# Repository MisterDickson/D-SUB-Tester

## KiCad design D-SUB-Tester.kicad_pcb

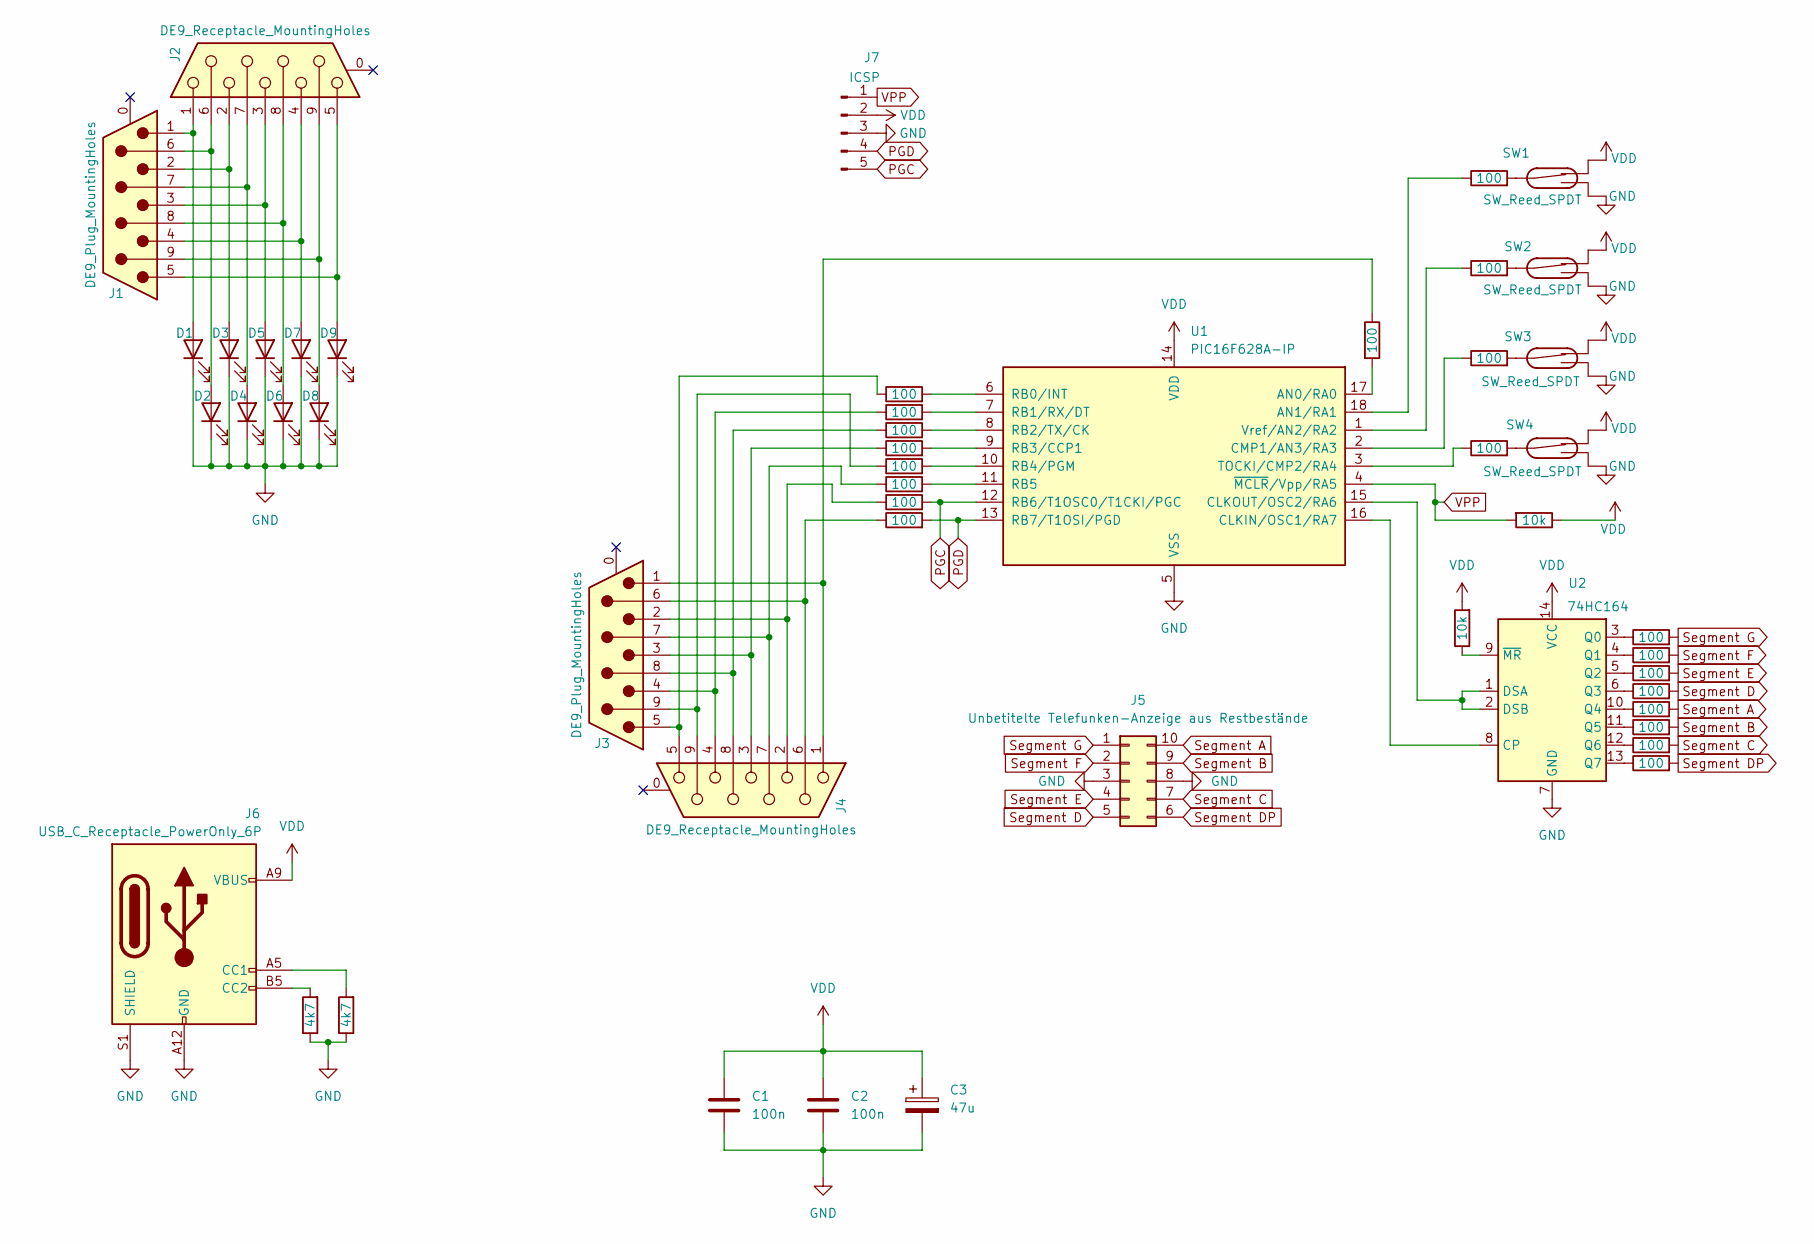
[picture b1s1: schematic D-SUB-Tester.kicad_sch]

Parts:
C1, C2: 100n; C_Disc_D7.0mm_W2.5mm_P5.00mm
C3: 47u; CP_Radial_D6.3mm_P2.50mm
D1, D2, D3, D4, D5, D6, D7, D8, D9: LED; LED_D3.0mm
J1, J3: DE9_Plug_MountingHoles; DSUB-9_Male_Horizontal_P2.77x2.84mm_EdgePinOffset7.70mm_Hou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
J2, J4: DE9_Receptacle_MountingHoles; DSUB-9_Female_Vertical_P2.77x2.84mm_MountingHoles
J5: Unbetitelte Telefunken-Anzeige aus Restbestände; DIP-10_W7.62mm_LongPads
J6: USB_C_Receptacle_PowerOnly_6P; USB_C_Receptacle_HRO_TYPE-C-31-M-17
J7: ICSP; PinHeader_1x05_P2.54mm_Vertical
R1, R2, R3, R4, R5, R6, R7, R8, R11, R12, R13, R14, R17, R18, R19, R20, R21, R22, R23, R24, R25: 100; R_Axial_DIN0411_L9.9mm_D3.6mm_P12.70mm_Horizontal
R9, R10: 4k7; R_Axial_DIN0411_L9.9mm_D3.6mm_P12.70mm_Horizontal
R15, R16: 10k; R_Axial_DIN0411_L9.9mm_D3.6mm_P12.70mm_Horizontal
SW1, SW2, SW3, SW4: SW_Reed_SPDT; SW_SPDT_CK_JS102011SAQN
U1: PIC16F628A-IP; DIP-18_W7.62mm_LongPads
U2: 74HC164; DIP-14_W7.62mm_LongPads

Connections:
GND: C1.2, C2.2, C3.2, D1.1 (K), D2.1 (K), D3.1 (K), D4.1 (K), D5.1 (K), D6.1 (K), D7.1 (K), D8.1 (K), D9.1 (K), J5.3, J5.8, J6.A12 (GND), J6.B12 (GND), J6.S1 (SHIELD), J7.3, R9.1, R10.1, SW1.3, SW2.3, SW3.3, SW4.3, U1.5 (VSS), U2.7 (GND)
unnamed: D1.2 (A), J1.1, J2.1
unnamed: D2.2 (A), J1.6, J2.6
unnamed: D3.2 (A), J1.2, J2.2
unnamed: D4.2 (A), J1.7, J2.7
unnamed: D5.2 (A), J1.3, J2.3
unnamed: D6.2 (A), J1.8, J2.8
unnamed: D7.2 (A), J1.4, J2.4
unnamed: D8.2 (A), J1.9, J2.9
unnamed: D9.2 (A), J1.5, J2.5
unnamed: J3.1, J4.1, R25.1
unnamed: J3.2, J4.2, R23.1
unnamed: J3.3, J4.3, R20.1
unnamed: J3.4, J4.4, R18.1
unnamed: J3.5, J4.5, R17.1
unnamed: J3.6, J4.6, R24.1
unnamed: J3.7, J4.7, R22.1
unnamed: J3.8, J4.8, R19.1
unnamed: J3.9, J4.9, R21.1
unnamed: J6.A5 (CC1), R10.2
unnamed: J6.B5 (CC2), R9.2
unnamed: R11.2, SW1.2
unnamed: R12.2, SW2.2
unnamed: R13.2, SW3.2
unnamed: R14.2, SW4.2
unnamed: R25.2, U1.17 (AN0/RA0)
unnamed: R11.1, U1.18 (AN1/RA1)
unnamed: U1.16 (CLKIN/OSC1/RA7), U2.8 (CP)
unnamed: U1.15 (CLKOUT/OSC2/RA6), U2.1 (DSA), U2.2 (DSB)
unnamed: R13.1, U1.2 (CMP1/AN3/RA3)
unnamed: R17.2, U1.6 (RB0/INT)
unnamed: R18.2, U1.7 (RB1/RX/DT)
unnamed: R19.2, U1.8 (RB2/TX/CK)
unnamed: R20.2, U1.9 (RB3/CCP1)
unnamed: R21.2, U1.10 (RB4/PGM)
unnamed: R22.2, U1.11 (RB5)
unnamed: R14.1, U1.3 (TOCKI/CMP2/RA4)
unnamed: R12.1, U1.1 (Vref/AN2/RA2)
unnamed: R1.1, U2.3 (Q0)
unnamed: R2.1, U2.4 (Q1)
unnamed: R3.1, U2.5 (Q2)
unnamed: R4.1, U2.6 (Q3)
unnamed: R5.1, U2.10 (Q4)
unnamed: R6.1, U2.11 (Q5)
unnamed: R7.1, U2.12 (Q6)
unnamed: R8.1, U2.13 (Q7)
unnamed: R15.1, U2.9 (~MR)
PGC: J7.5, R23.2, U1.12 (RB6/T1OSC0/T1CKI/PGC)
PGD: J7.4, R24.2, U1.13 (RB7/T1OSI/PGD)
Segment A: J5.10, R5.2
Segment B: J5.9, R6.2
Segment C: J5.7, R7.2
Segment D: J5.5, R4.2
Segment DP: J5.6, R8.2
Segment E: J5.4, R3.2
Segment F: J5.2, R2.2
Segment G: J5.1, R1.2
VDD: C1.1, C2.1, C3.1, J6.A9 (VBUS), J6.B9 (VBUS), J7.2, R15.2, R16.1, SW1.1, SW2.1, SW3.1, SW4.1, U1.14 (VDD), U2.14 (VCC)
VPP: J7.1, R16.2, U1.4 (~MCLR/Vpp/RA5)

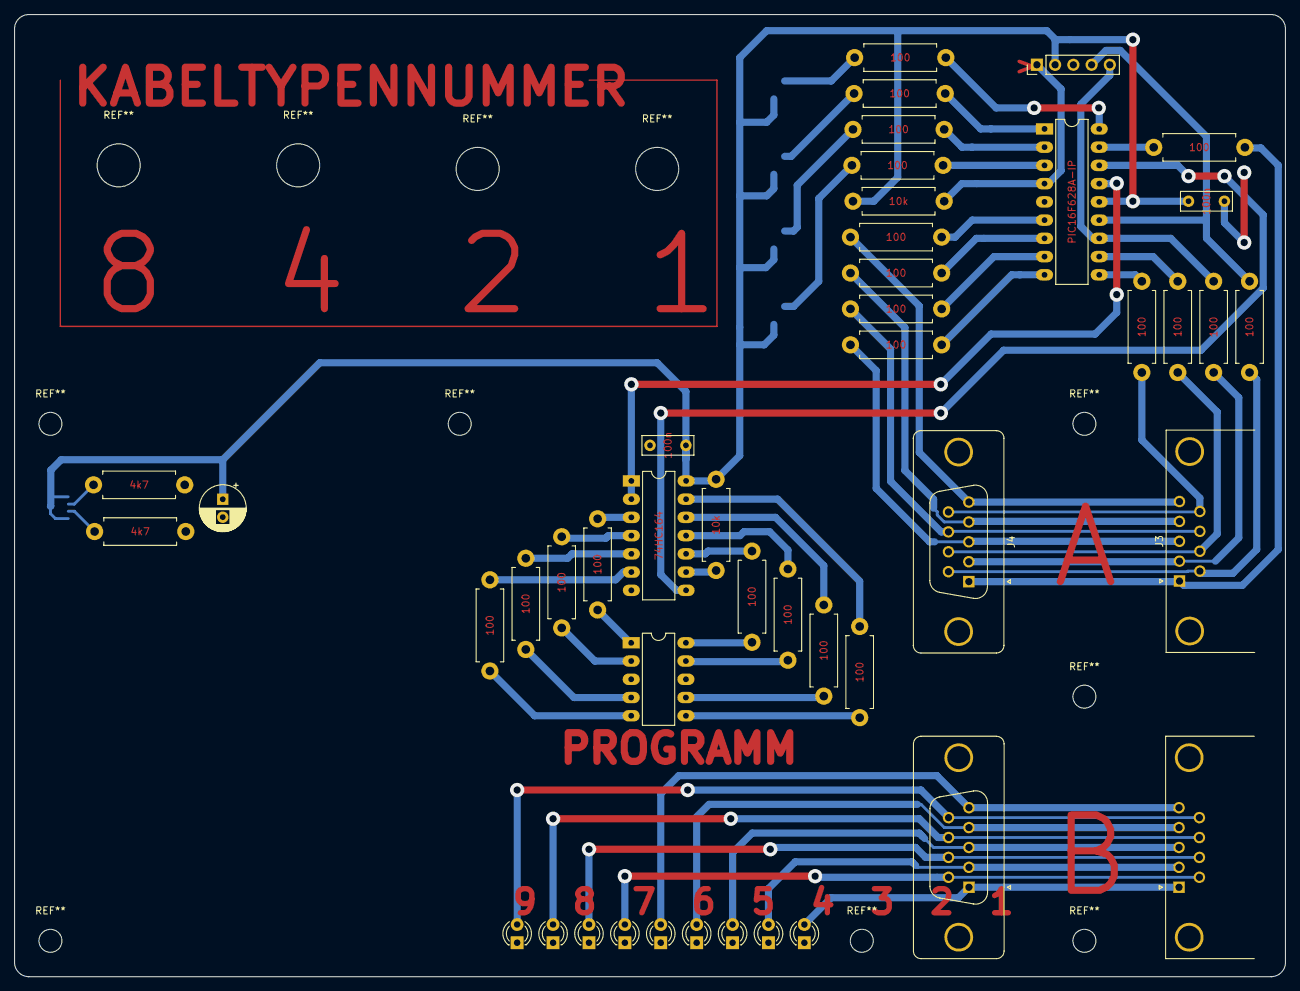
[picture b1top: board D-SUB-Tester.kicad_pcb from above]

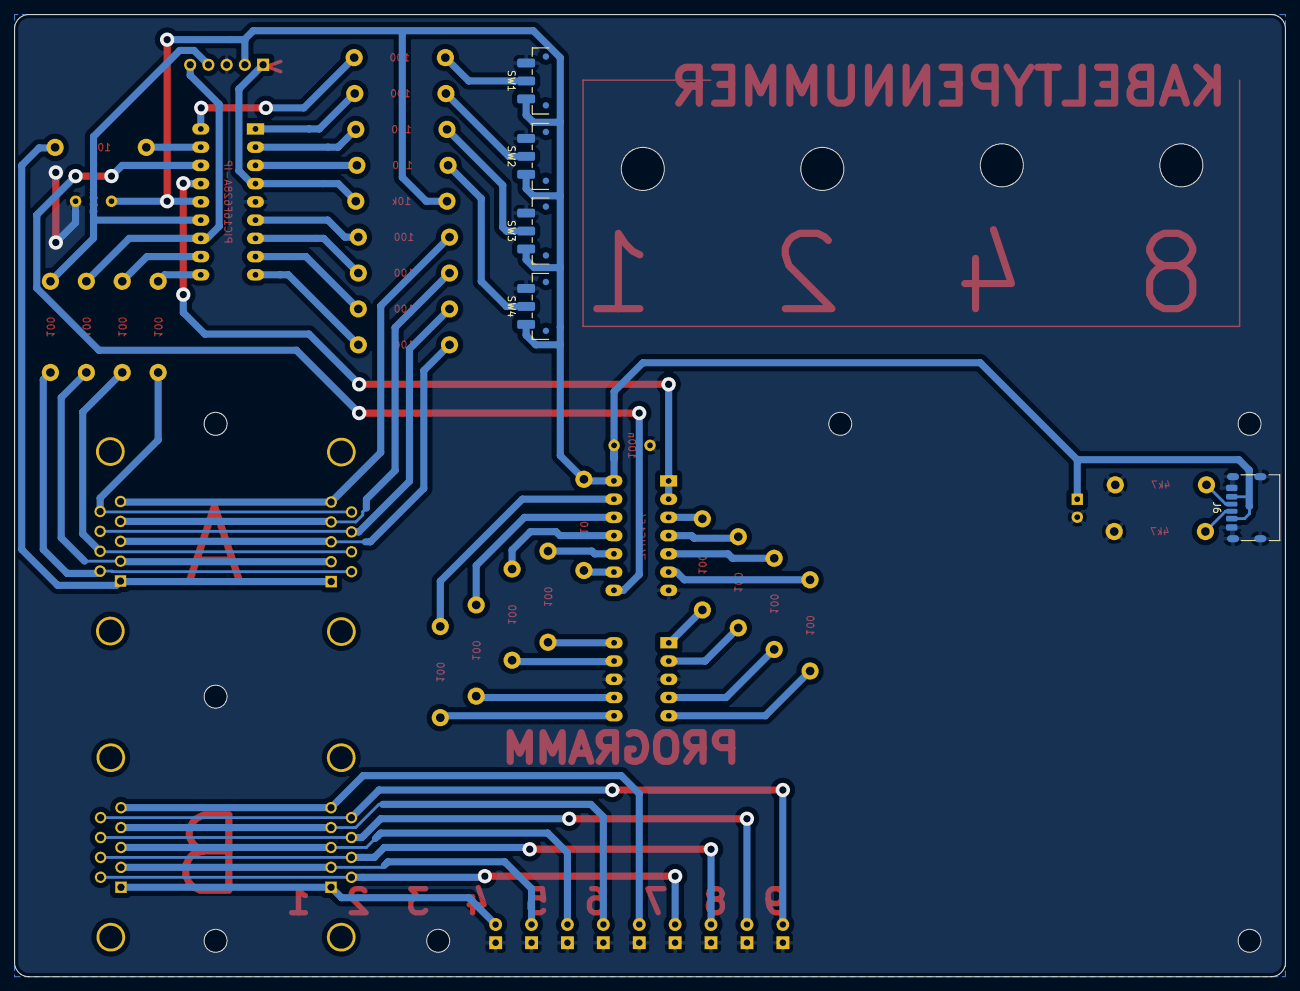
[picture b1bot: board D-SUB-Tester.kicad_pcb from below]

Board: 2 copper layers, 177.0 x 134.0 mm, 50 parts (5 on the bottom side), 59 nets.

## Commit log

2025-01-14 init
2025-01-14 quick save
2025-01-14 EVT 1
2025-01-20 V1 RC
2025-01-20 add fabrication files
2025-01-21 change usb drillings to smd pads
2025-01-21 fabrication of V1 RC2
2025-01-21 V1 RC3 - fix some drillings
